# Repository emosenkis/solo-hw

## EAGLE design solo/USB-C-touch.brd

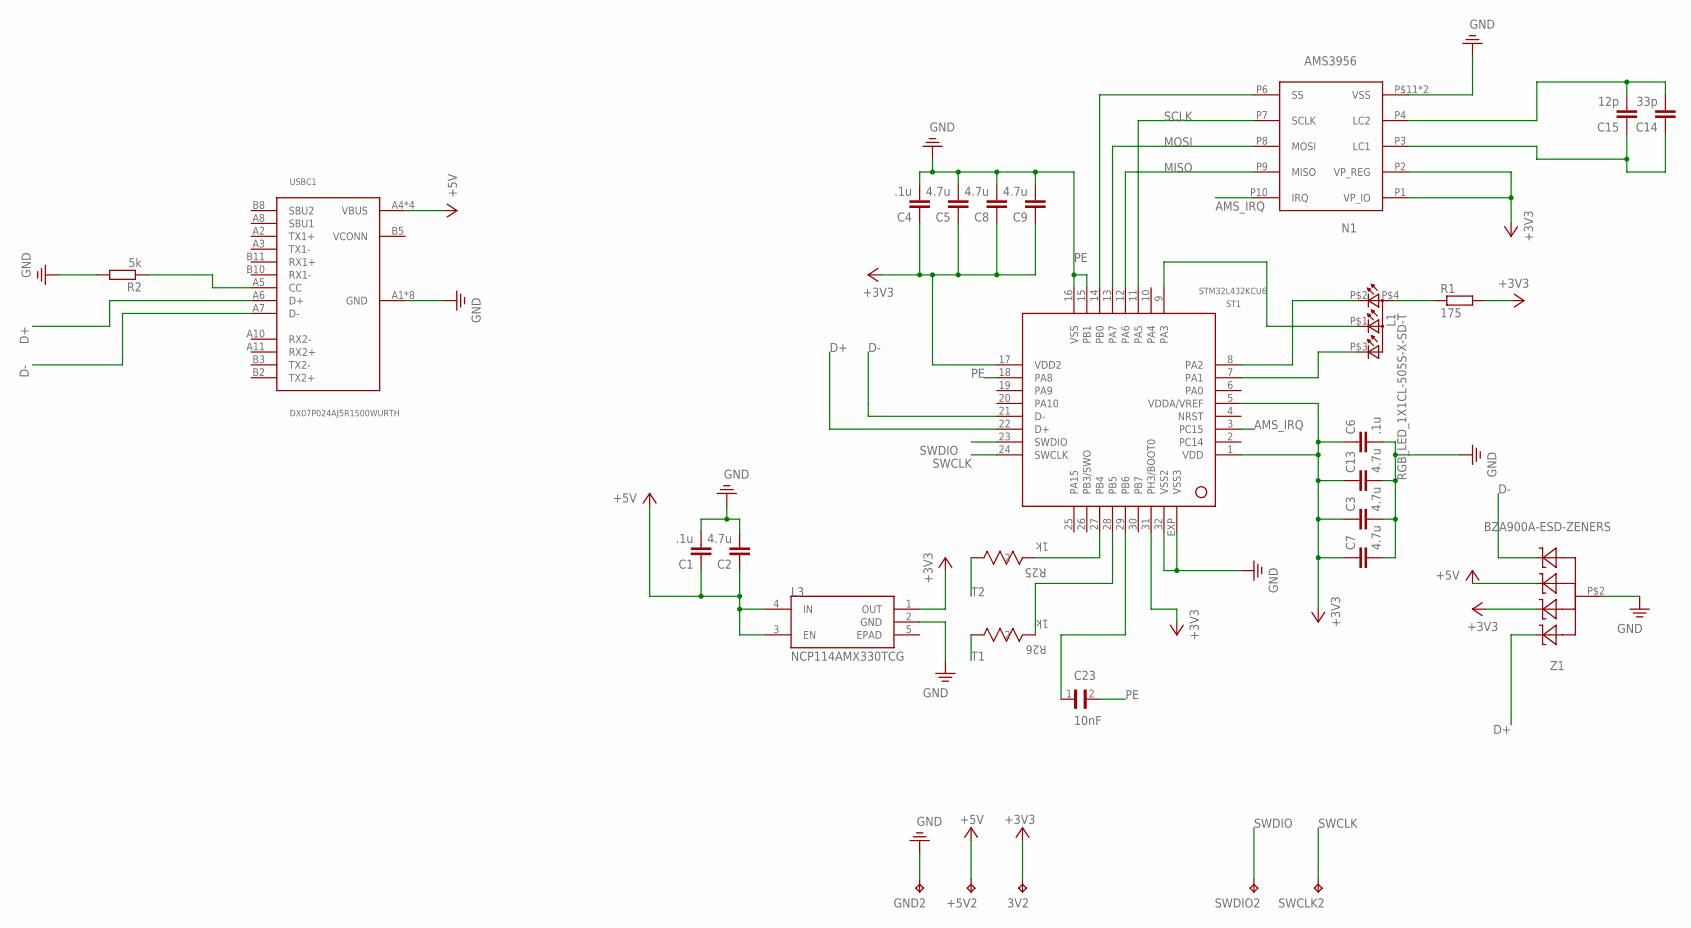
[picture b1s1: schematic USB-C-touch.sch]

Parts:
3V2: TEST_POINT; B1,27
+5V2: TEST_POINT; B1,27
C1, C4, C6: .1u; C0402
C2, C3, C5, C7, C8, C9, C13: 4.7u; C0402
C14: 33p; C0402
C15: 12p; C0402
C23: 10nF; CAPC2012X95N
GND2: TEST_POINT; B1,27
L1: RGB_LED_1X1CL-505S-X-SD-T; CL-505S-X-SD-T
L3: NCP114AMX330TCG; REG_NCP114AMX330TCG
N1: AMS3956; MLPD3X3
R1: 175; R0402
R2: 5k; R0402
R25, R26: 1k; RC0402N-L
ST1: STM32L432KCU6; QFN32
SWCLK2: TEST_POINT; B1,27
SWDIO2: TEST_POINT; B1,27
USBC1: DX07P024AJ5R1500WURTH; WüRTH_632712000112
Z1: BZA900A-ESD-ZENERS; BZA900A

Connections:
+3V3: 3V2.TP, C3.1, C4.1, C5.1, C6.1, C7.1, C8.1, C9.1, C13.1, L3.1 (OUT), N1.P1 (VP_IO), N1.P2 (VP_REG), R1.2, ST1.1 (VDD), ST1.5 (VDDA/VREF), ST1.17 (VDD2), ST1.31 (PH3/BOOT0), Z1.P$5 (C1)
+5V: +5V2.TP, C1.1, C2.1, L3.3 (EN), L3.4 (IN), USBC1.A4 (VBUS), USBC1.A9 (VBUS), USBC1.B4 (VBUS), USBC1.B9 (VBUS), Z1.P$1 (C)
AMS_CS1: N1.P6 (SS), ST1.14 (PB0)
AMS_IRQ: N1.P10 (IRQ), ST1.3 (PC15)
D+: ST1.22 (D+), USBC1.A6 (D+), Z1.P$3 (C3)
D-: ST1.21 (D-), USBC1.A7 (D-), Z1.P$4 (C2)
MISO: N1.P9 (MISO), ST1.12 (PA6)
MOSI: N1.P8 (MOSI), ST1.13 (PA7)
unnamed: R2.1, USBC1.A5 (CC)
unnamed: L1.P$4 (A2), R1.1
unnamed: L1.P$2 (CRED), ST1.8 (PA2)
unnamed: L1.P$1 (CBLUE), ST1.9 (PA3)
unnamed: L1.P$3 (CGREEN), ST1.7 (PA1)
unnamed: C14.2, C15.2, N1.P4 (LC2)
unnamed: C14.1, C15.1, N1.P3 (LC1)
PE: C1.2, C2.2, C3.2, C4.2, C5.2, C6.2, C7.2, C8.2, C9.2, C13.2, C23.2, GND2.TP, L3.2 (GND), N1.P5 (VSS), N1.P$11 (VSS), R2.2, ST1.15 (PB1), ST1.16 (VSS), ST1.18 (PA8), ST1.32 (VSS2), ST1.EXP (VSS3), USBC1.A1 (GND), USBC1.A12 (GND), USBC1.B1 (GND), USBC1.B12 (GND), USBC1.P_GND1 (GND), USBC1.P_GND2 (GND), USBC1.P_GND3 (GND), USBC1.P_GND4 (GND), Z1.P$2
S$2: R26.2, ST1.28 (PB5)
S$4: R25.2, ST1.27 (PB4)
S$5: C23.1, ST1.29 (PB6)
SCLK: N1.P7 (SCLK), ST1.11 (PA5)
SWCLK: ST1.24 (SWCLK), SWCLK2.TP
SWDIO: ST1.23 (SWDIO), SWDIO2.TP
T1: R26.1
T2: R25.1

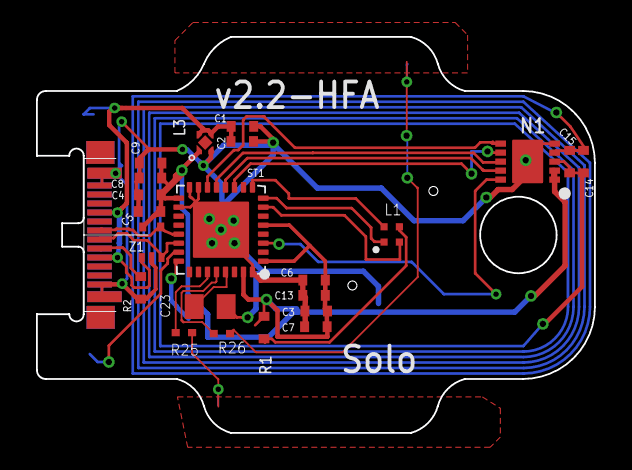
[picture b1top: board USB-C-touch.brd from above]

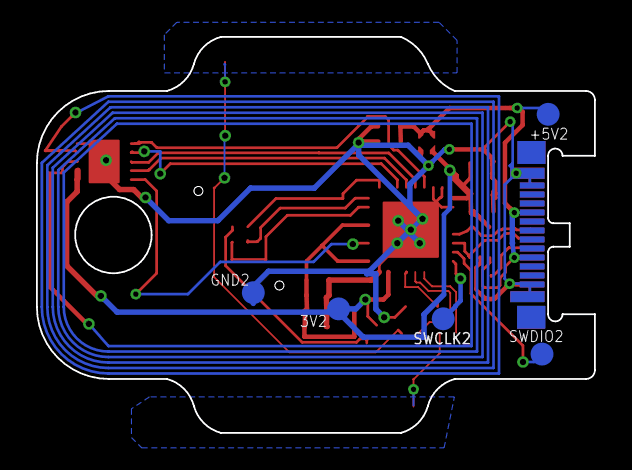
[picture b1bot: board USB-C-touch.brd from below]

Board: 2 copper layers, 31.0 x 22.0 mm, 28 parts (5 on the bottom side), 22 nets.

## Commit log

2019-12-22 Solo Touch C: Move around component names to ensure they're legible and on the proper layer to be printed on the board.
2019-12-22 Add touch variant of Solo USB C Tap.
2019-12-22 Add OpenJSCAD file for USB C Touch case.
